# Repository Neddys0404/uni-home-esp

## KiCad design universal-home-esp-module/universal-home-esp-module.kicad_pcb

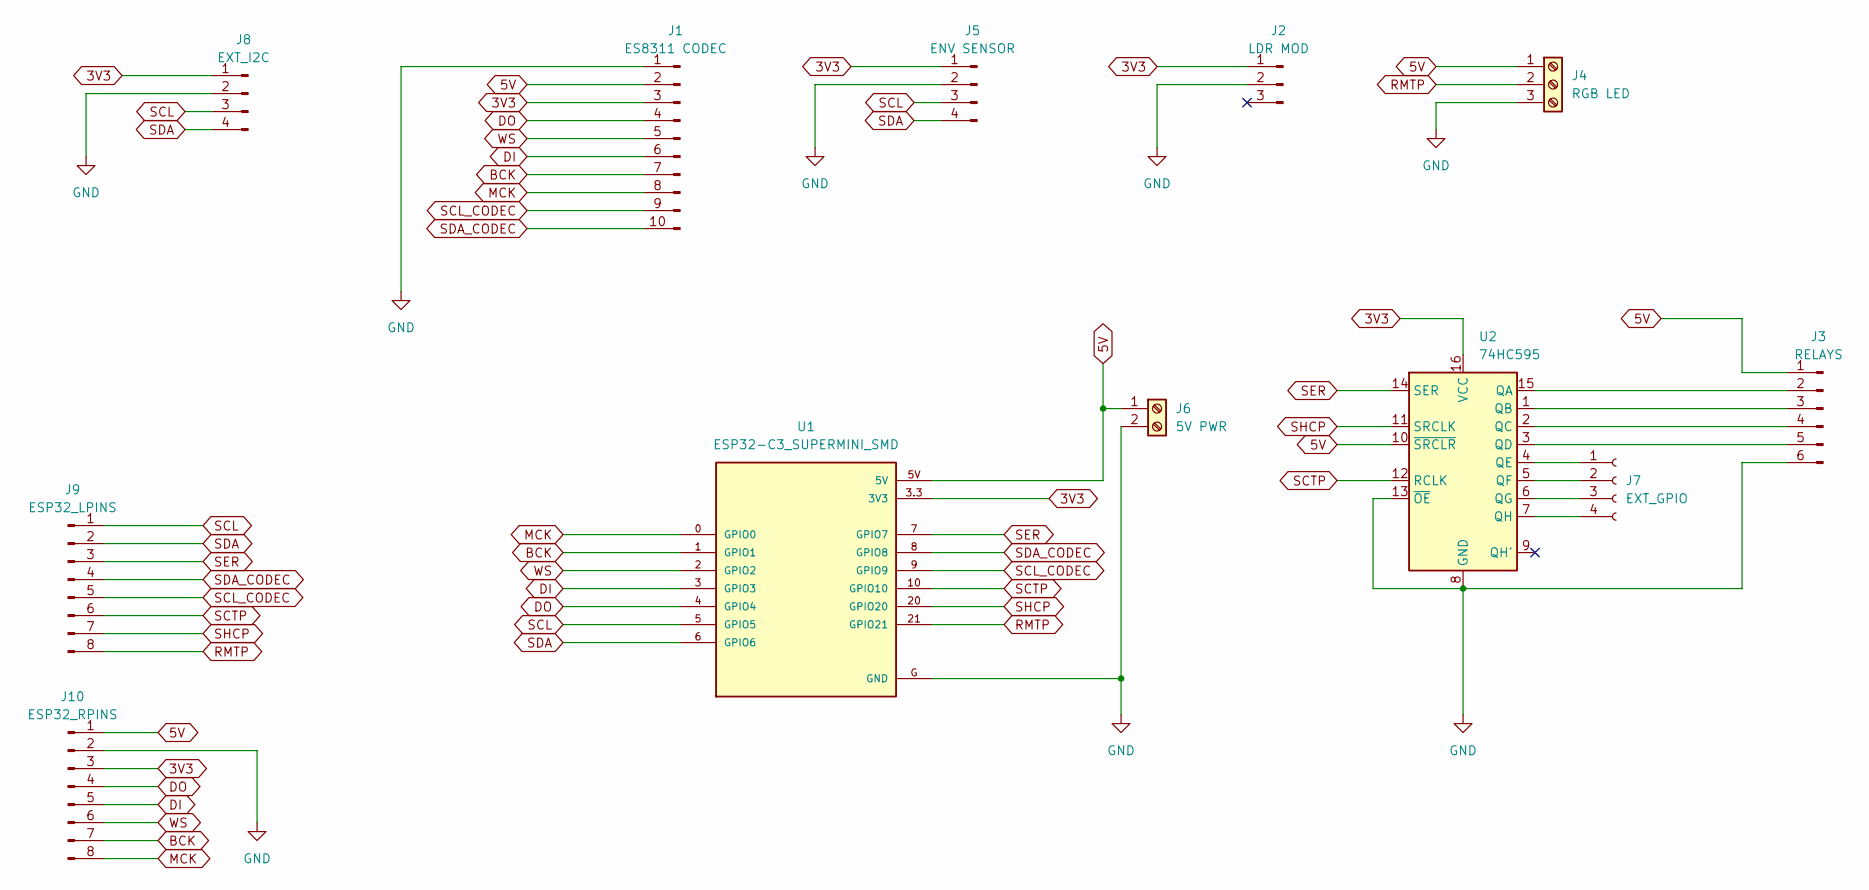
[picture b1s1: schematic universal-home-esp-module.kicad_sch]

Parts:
J1: ES8311 CODEC; PinHeader_1x10_P2.54mm_Vertical
J2: LDR MOD; PinHeader_1x03_P2.54mm_Vertical
J3: RELAYS; PinHeader_1x06_P2.54mm_Vertical
J4: RGB LED; TerminalBlock_RND_205-00233_1x03_P5.08mm_Horizontal
J5: ENV SENSOR; PinHeader_1x04_P2.54mm_Vertical
J6: 5V PWR; TerminalBlock_RND_205-00232_1x02_P5.08mm_Horizontal
J7: EXT_GPIO; PinHeader_1x04_P2.54mm_Vertical
J8: EXT_I2C; PinHeader_1x04_P2.54mm_Vertical
J9: ESP32_LPINS; PinHeader_1x08_P2.54mm_Vertical
J10: ESP32_RPINS; PinHeader_1x08_P2.54mm_Vertical
U1: ESP32-C3_SUPERMINI_SMD; MODULE_ESP32-C3_SUPERMINI
U2: 74HC595; DIP-16_W7.62mm_LongPads

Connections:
3V3: J1.3, J2.1, J5.1, J8.1, J10.3, U1.3.3 (3V3), U2.16 (VCC)
5V: J1.2, J3.1, J4.1, J6.1, J10.1, U1.5V, U2.10 (~SRCLR)
BCK: J1.7, J10.7, U1.1 (GPIO1)
DI: J1.6, J10.5, U1.3 (GPIO3)
DO: J1.4, J10.4, U1.4 (GPIO4)
GND: J1.1, J2.2, J3.6, J4.3, J5.2, J6.2, J8.2, J10.2, U1.G (GND), U2.8 (GND), U2.13 (~OE)
MCK: J1.8, J10.8, U1.0 (GPIO0)
unnamed: J3.2, U2.15 (QA)
unnamed: J3.3, U2.1 (QB)
unnamed: J3.4, U2.2 (QC)
unnamed: J3.5, U2.3 (QD)
unnamed: J7.1, U2.4 (QE)
unnamed: J7.2, U2.5 (QF)
unnamed: J7.3, U2.6 (QG)
unnamed: J7.4, U2.7 (QH)
RMTP: J4.2, J9.8, U1.21 (GPIO21)
SCL: J5.3, J8.3, J9.1, U1.5 (GPIO5)
SCL_CODEC: J1.9, J9.5, U1.9 (GPIO9)
SCTP: J9.6, U1.10 (GPIO10), U2.12 (RCLK)
SDA: J5.4, J8.4, J9.2, U1.6 (GPIO6)
SDA_CODEC: J1.10, J9.4, U1.8 (GPIO8)
SER: J9.3, U1.7 (GPIO7), U2.14 (SER)
SHCP: J9.7, U1.20 (GPIO20), U2.11 (SRCLK)
WS: J1.5, J10.6, U1.2 (GPIO2)

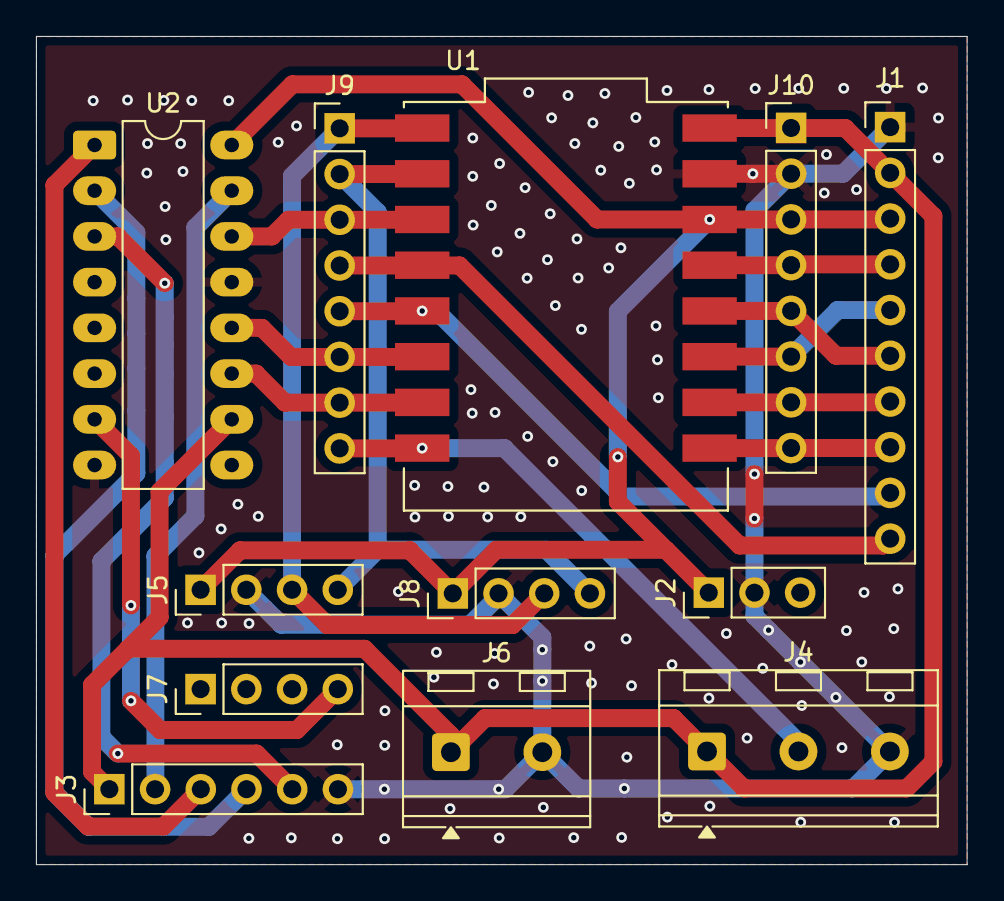
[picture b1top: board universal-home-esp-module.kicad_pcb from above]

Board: 2 copper layers, 51.7 x 46.0 mm, 12 parts (0 on the bottom side), 24 nets.
